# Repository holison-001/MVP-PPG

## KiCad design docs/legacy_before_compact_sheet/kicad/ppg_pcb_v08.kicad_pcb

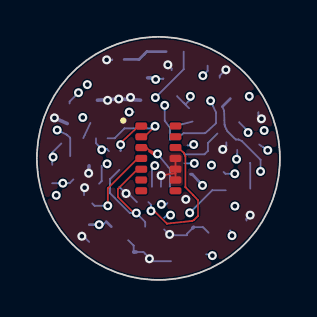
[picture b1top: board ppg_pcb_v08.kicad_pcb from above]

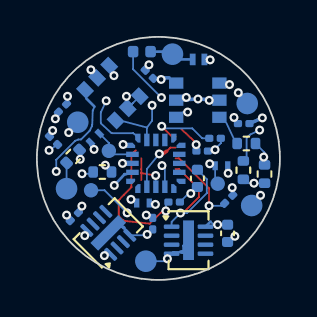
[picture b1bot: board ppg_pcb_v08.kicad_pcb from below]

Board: 4 copper layers, 13.5 x 13.5 mm, 37 parts (36 on the bottom side), 22 nets.

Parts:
C1: 10uF 6.3V X5R; C_0402_1005Metric
C4, C5, C12, C14: 1uF 6.3V; C_0201_0603Metric
C6, C7, C11: 100nF; C_0201_0603Metric
C13: 1uF 25V X7R; C_0402_1005Metric
D1: SPHV15-01ETG; TVS_SOD882_1x0.6
D6, D7, D8: ESD351DPYR; TI_DPY0002A_1x0.6
FB1: BLM15PX601SN1D; L_0402_1005Metric
J1: 12V; CablePad_D1.2
J2: GND; CablePad_D1.2
J3: TXP; CablePad_D1.2
J4: TXN; CablePad_D1.2
J5: RXP; CablePad_D1.2
J6: RXN; CablePad_D1.2
J7: SWDIO; CablePad_D0.8
J8: SWCLK; CablePad_D0.8
J9: NRST; CablePad_D0.8
R1, R2: 4.7k; R_0201_0603Metric
R3: 120/1%; R_0402_1005Metric
R4: 10k; R_0201_0603Metric
R5, R6, R7, R8: 22; R_0402_1005Metric
U1: MAXM86161EFD+; MAXM86161_OLGA-14
U2: STM32C011F6U6; ST_UFQFPN-20_3x3mm_P0.5mm
U3: XR33194; TSOT23-6_MaxLinear
U4: MCP1703A-5002E/MC; DFN-8-1EP_2x3mm_P0.5mm_EP0.61x2.2mm
U5: MCP1703A-3302E/MC; DFN-8-1EP_2x3mm_P0.5mm_EP0.61x2.2mm
U6: XR33183; TSOT23-6_MaxLinear

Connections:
3V3: C6.1, C7.1, C11.1, C12.1, C14.1, R1.2, R2.2, R4.2, U1.3, U2.2, U3.2, U3.3, U5.1, U6.1
5V_LED: C1.1, U1.5, U4.1, U5.8
12V: C13.1, FB1.2, U4.8
/12V_IN: D1.1 (K), FB1.1, J1.1
/NRST: D8.1 (IO/K), J9.1, U2.4
/RXN: J6.1, R3.2, R8.2
/RXN_RCV: R8.1, U6.4
/RXP: J5.1, R3.1, R7.2
/RXP_RCV: R7.1, U6.6
/SCL: R2.1, U1.2, U2.18
/SDA: R1.1, U1.1, U2.19
/SWCLK: D7.1 (IO/K), J8.1, U2.17
/SWDIO: D6.1 (IO/K), J7.1, U2.16
/TXN: J4.1, R6.2
/TXN_DRV: R6.1, U3.4
/TXP: J3.1, R5.2
/TXP_DRV: R5.1, U3.6
/UART_RX: U2.15, U6.3
/UART_TX: R4.1, U2.14, U3.1
/VLDO: C4.1, U1.4
/VREF: C5.1, U1.12
GND: C1.2, C4.2, C5.2, C6.2, C7.2, C11.2, C12.2, C13.2, C14.2, D1.2 (A), D6.2 (GND/A), D7.2 (GND/A), D8.2 (GND/A), J2.1, U1.9, U1.10, U1.11, U2.3, U3.5, U4.4, U4.9, U5.4, U5.9, U6.2, U6.5
